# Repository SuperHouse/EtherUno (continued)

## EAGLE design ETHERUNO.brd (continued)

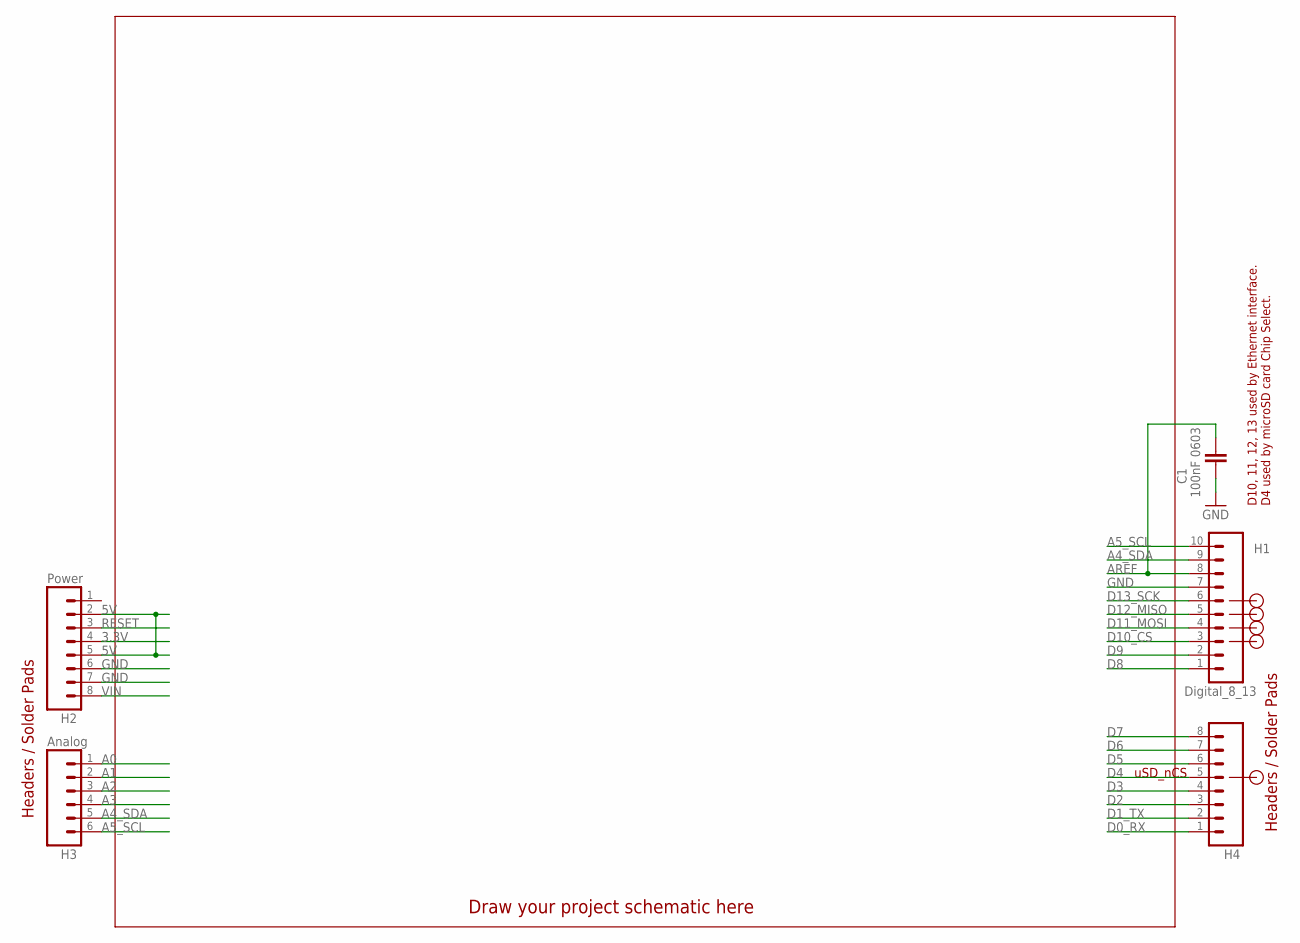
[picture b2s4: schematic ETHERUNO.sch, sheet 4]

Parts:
C1: 100nF 0603; C0603
H1: Digital_8_13; 1X10-S
H2: Power; 1X08-S
H3: Analog; 1X06-S
H4: Digital_0_7; 1X08-S

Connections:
3.3V: H2.4; also elsewhere on the board
5V: H2.2, H2.5; also elsewhere on the board
A0: H3.1; also elsewhere on the board
A1: H3.2; also elsewhere on the board
A2: H3.3; also elsewhere on the board
A3: H3.4; also elsewhere on the board
A4_SDA: H1.9, H3.5; also elsewhere on the board
A5_SCL: H1.10, H3.6; also elsewhere on the board
AREF: C1.1, H1.8; also elsewhere on the board
D0_RX: H4.1; also elsewhere on the board
D1_TX: H4.2; also elsewhere on the board
D2: H4.3; also elsewhere on the board
D3: H4.4; also elsewhere on the board
D4: H4.5; also elsewhere on the board
D5: H4.6; also elsewhere on the board
D6: H4.7; also elsewhere on the board
D7: H4.8; also elsewhere on the board
D8: H1.1; also elsewhere on the board
D9: H1.2; also elsewhere on the board
D10_CS: H1.3; also elsewhere on the board
D11_MOSI: H1.4; also elsewhere on the board
D12_MISO: H1.5; also elsewhere on the board
D13_SCK: H1.6; also elsewhere on the board
GND: C1.2, H1.7, H2.6, H2.7; also elsewhere on the board
RESET: H2.3; also elsewhere on the board
VIN: H2.8; also elsewhere on the board

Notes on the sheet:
Headers / Solder Pads
Draw your project schematic here
D10, 11, 12, 13 used by Ethernet interface.
uSD_nCS
D4 used by microSD card Chip Select.

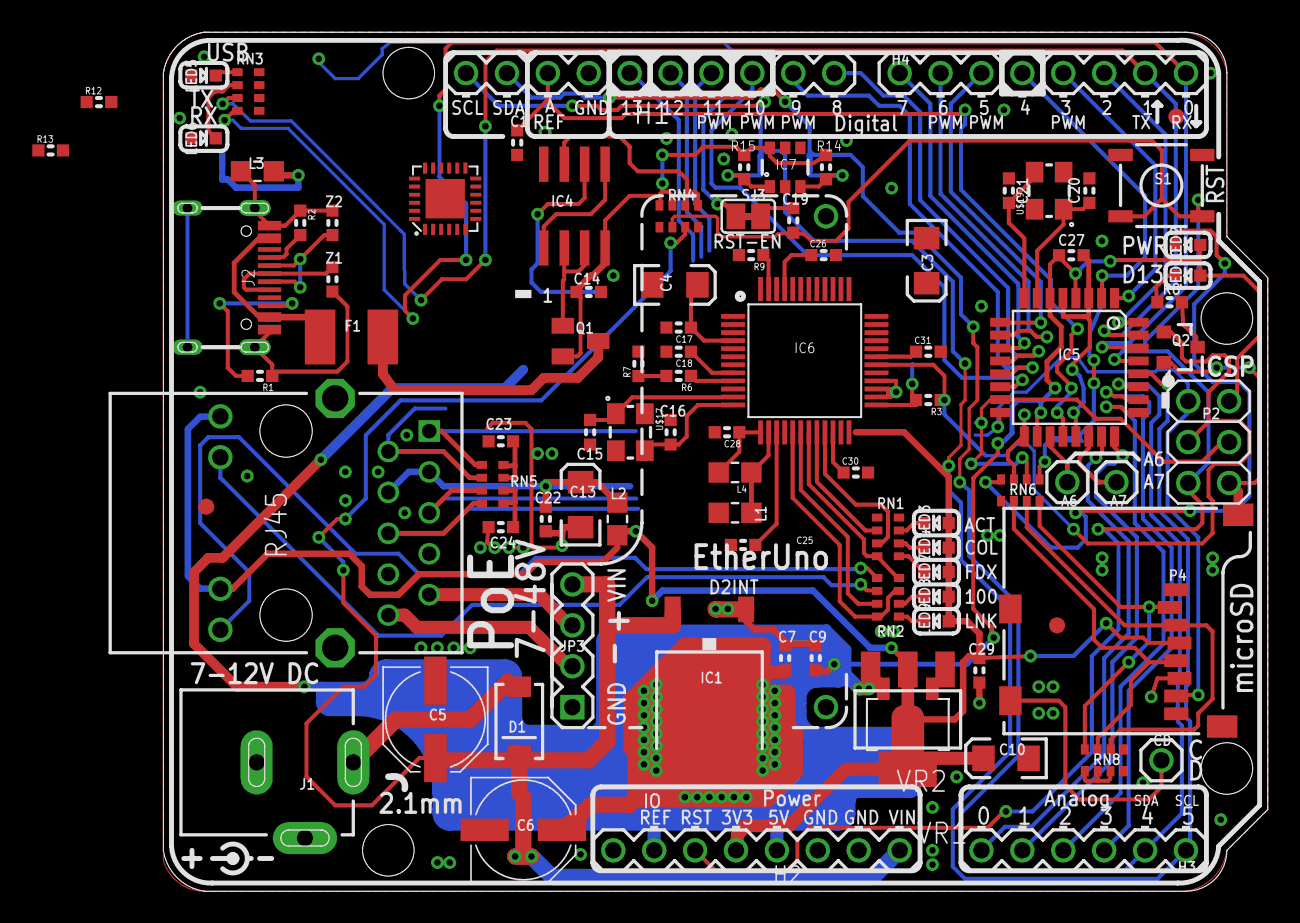
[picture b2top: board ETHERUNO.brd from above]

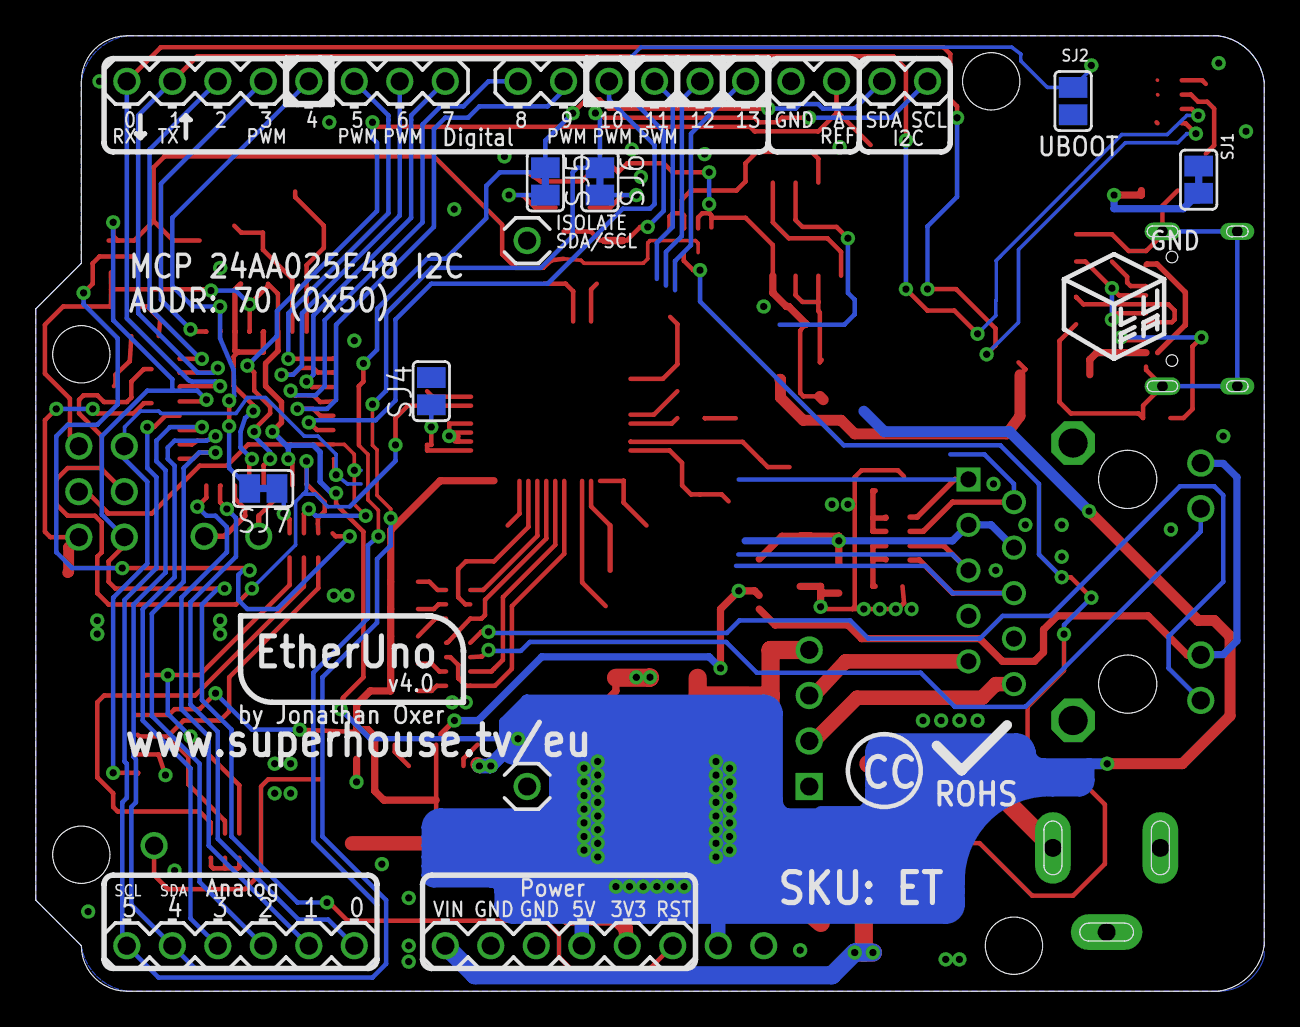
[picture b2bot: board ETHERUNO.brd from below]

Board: 2 copper layers, 68.6 x 53.3 mm, 98 parts (6 on the bottom side), 91 nets.

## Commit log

2019-04-23 Renamed project files
2019-04-23 Ethernet chip conversion
2020-05-15 Beginning of conversion to USB-C and W5100S
2020-05-15 Added cut-track jumper to isolate D4
2020-05-27 Split schematic into separate sheets
2020-07-01 Major rework of schematic to suit W6100
2020-07-06 Removed ATmega16U2 and added CP2102N for USB-serial conversion
2020-07-17 Final routing and DRC for v4.0 release
2020-07-17 Added render image
2020-08-06 Major rework for W5500, ready for v1.0 release
2020-09-08 Added images
2020-09-10 Added W5500 datasheet
2020-09-10 Fix Ethernet data line bias resistors. Add strong pullups and pulldowns to mode and RSVD pins. Improve silkscreen. Add diode to PoE VIN to protect against backpower.
2020-09-10 Updated timesheet
2020-09-10 Removed timesheet
2020-09-10 Added gitignore file
2020-09-10 Fixed name
2020-09-17 Added cut-track jumper to isolate D4 from SD_CS
2020-09-27 Added .gitignore
2020-09-27 Added image of v1.1 prototype.
2020-09-27 Added timesheet to .gitignore
